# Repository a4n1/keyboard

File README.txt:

Low-profile, diode-less, 36-key, Bluetooth keyboard. Designed with Ergogen and Kicad.

Prerequisites:
nix

Build PCB files:
nix run

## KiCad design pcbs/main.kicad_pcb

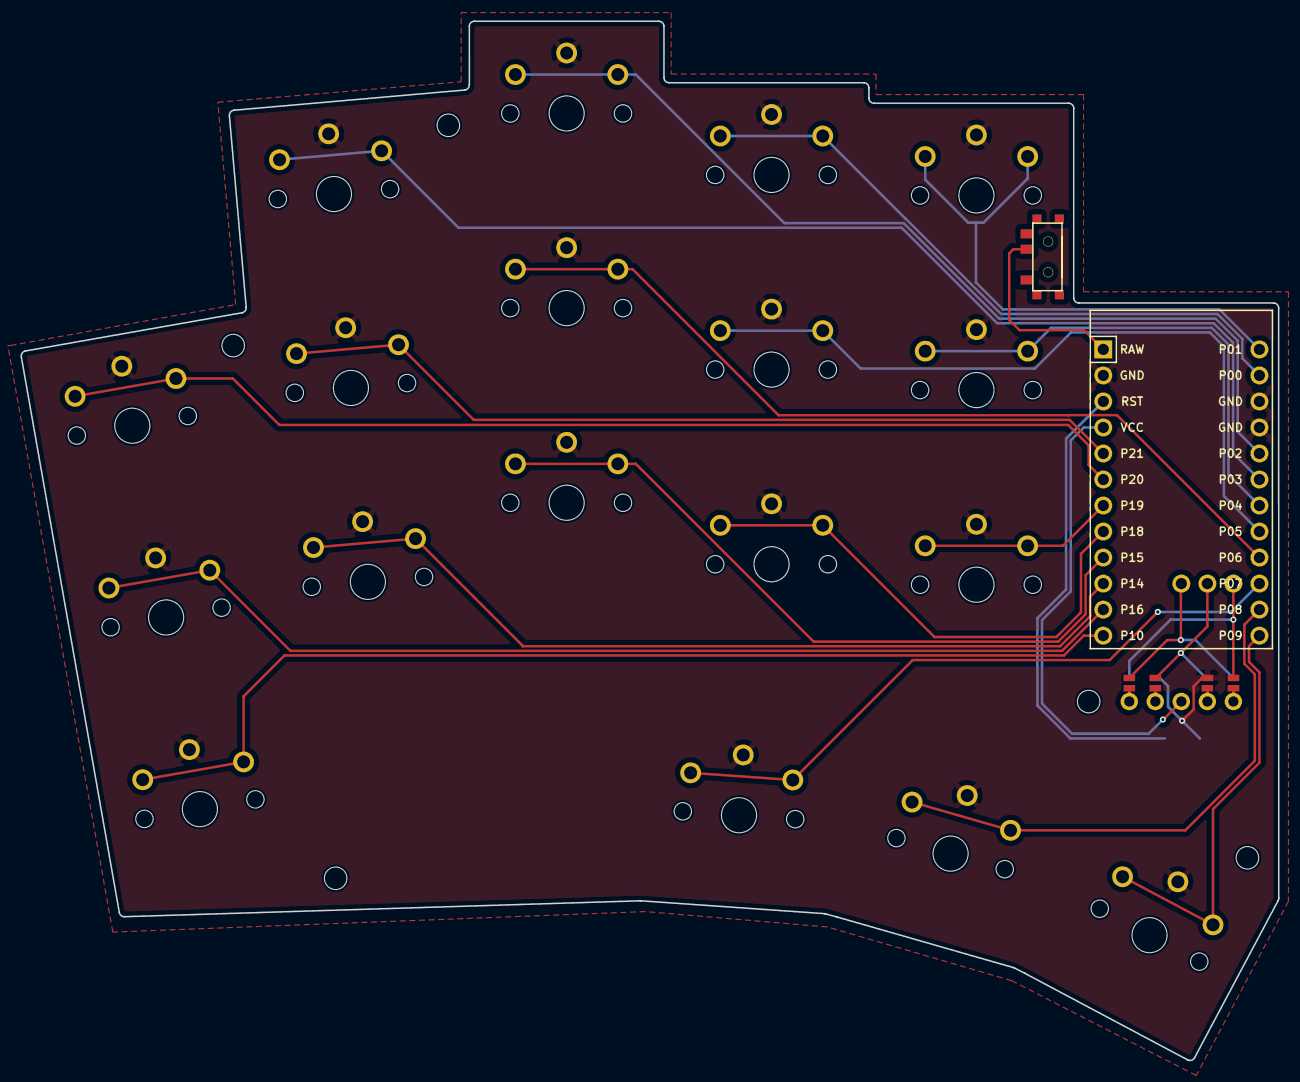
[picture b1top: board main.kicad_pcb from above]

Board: 2 copper layers, 122.7 x 101.4 mm, 21 parts (0 on the bottom side), 24 nets.

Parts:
MCU1: ProMicro
S1, S2, S3, S4, S5, S6, S7, S8, S9, S10, S11, S12, S13, S14, S15, S16, S17, S18: PG1350
T1: SPDT_C128955
nice!view1: nice!view; niceview

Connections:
CS: MCU1.31, nice!view1.1, nice!view1.5
GND: MCU1.2, MCU1.15, MCU1.16, S1.2, S2.2, S3.2, S4.2, S5.2, S6.2, S7.2, S8.2, S9.2, S10.2, S11.2, S12.2, S13.2, S14.2, S15.2, S16.2, S17.2, S18.2, nice!view1.2, nice!view1.4
MOSI: MCU1.33, nice!view1.1, nice!view1.5
RAW: MCU1.1, T1.2
SCK: MCU1.32, nice!view1.2, nice!view1.4
VCC: MCU1.4, nice!view1.3
keys_index_bottom: MCU1.8, S10.1
keys_index_home: MCU1.20, S11.1
keys_index_top: MCU1.14, S12.1
keys_inner_bottom: MCU1.7, S13.1
keys_inner_home: MCU1.19, S14.1
keys_inner_top: MCU1.13, S15.1
keys_middle_bottom: MCU1.9, S7.1
keys_middle_home: MCU1.21, S8.1
keys_middle_top: MCU1.17, S9.1
keys_pinky_bottom: MCU1.12, S1.1
keys_pinky_home: MCU1.11, S2.1
keys_pinky_top: MCU1.6, S3.1
keys_ring_bottom: MCU1.10, S4.1
keys_ring_home: MCU1.5, S5.1
keys_ring_top: MCU1.18, S6.1
keys_thumb_home: MCU1.23, S17.1
keys_thumb_inner: MCU1.22, S16.1
keys_thumb_outer: MCU1.24, S18.1

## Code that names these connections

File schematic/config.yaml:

meta:
  engine: 4.1.0
points:
  zones:
    keys:
      columns:
        pinky:
          key:
            splay: 10
        ring:
          key:
            stagger: 19 
            spread: 20 
            splay: -5
        middle:
          key:
            stagger: 6
            spread: 20 
            splay: -5
        index:
          key:
            stagger: -6
            spread: 20 
        inner:
          key:
            stagger: -2
            spread: 20 
      rows:
        bottom:
        home:
        top:
      anchor:
        shift: [150, -150]
    thumb:
      anchor:
        ref: keys_inner_bottom
        shift: [-1.2875cx, -1.25cx]
      columns:
        inner:
          key:
            splay: -4
            name: keys_thumb_inner
        home:
          key:
            splay: -12
            origin: [-10, -10]
            name: keys_thumb_home
        outer:
          key:
            splay: -12
            origin: [-10, -10]
            name: keys_thumb_outer
outlines:
  panel:
    - what: polygon
      operation: stack
      fillet: 0.5
      points:
        - ref: keys_pinky_top
          shift: [-0.5cx - 0.5, -0.5cx]
        - ref: keys_pinky_top
          shift: [-0.5cx - 0.5, 0.5cx]
        - ref: keys_pinky_top
          shift: [0.5cx + 3.915, 0.5cx]
        - ref: keys_ring_top
          shift: [-0.5cx - 0.5, 0.5cx]
        - ref: keys_ring_top
          shift: [0.5cx + 5.05, 0.5cx]
        - ref: keys_middle_top
          shift: [-0.5cx - 0.5, 0.5cx]
        - ref: keys_middle_top
          shift: [0.5cx + 0.5, 0.5cx]
        - ref: keys_index_top
          shift: [-0.5cx - 1.5, 0.5cx]
        - ref: keys_index_top
          shift: [0.5cx + 0.5, 0.5cx]
        - ref: keys_inner_top
          shift: [-0.5cx - 1.5, 0.5cx]
        - ref: keys_inner_top
          shift: [0.5cx + 0.5, 0.5cx]
        - ref: keys_inner_top
          shift: [0.5cx + 0.5, -0.5cx - 1.5]
        - ref: keys_inner_top
          shift: [1.5cx + 2.5, -0.5cx - 1.5]
        - ref: keys_thumb_outer
          shift: [0.5cx + 0.5, 0.5cx]
        - ref: keys_thumb_outer
          shift: [0.5cx + 0.5, -0.5cx]
        - ref: keys_thumb_outer
          shift: [-0.5cx, -0.5cx]
        - ref: keys_thumb_home
          shift: [0.5cx, -0.5cx]
        - ref: keys_thumb_home
          shift: [-0.5cx, -0.5cx]
        - ref: keys_thumb_inner
          shift: [0.5cx, -0.5cx]
        - ref: keys_thumb_inner
          shift: [-0.5cx, -0.5cx]
        - ref: keys_pinky_bottom
          shift: [-0.5cx - 0.5, -0.5cx]
pcbs:
  main:
    template: kicad8
    outlines:
      main:
        outline: panel
    footprints:
      choc_hotswap:
        what: choc
        where: true
        params:
          from: "{{name}}"
          to: GND
          keycaps: true
          reverse: true
          hotswap: false
      controller:
        what: nicenano
        where:
          - ref: keys_inner_bottom
            shift: [cx + 2, 0.5cx]
            rotate: -90
        params:
          P20: keys_pinky_top
          P16: keys_pinky_home
          P10: keys_pinky_bottom

          P3: keys_ring_top
          P21: keys_ring_home
          P14: keys_ring_bottom

          P2: keys_middle_top
          P6: keys_middle_home
          P15: keys_middle_bottom

          P0: keys_index_top
          P5: keys_index_home
          P18: keys_index_bottom

          P1: keys_inner_top
          P4: keys_inner_home
          P19: keys_inner_bottom

          P7: keys_thumb_inner
          P8: keys_thumb_home
          P9: keys_thumb_outer

          P33: MOSI
          P32: SCK
          P31: CS
      niceview:
        what: niceview
        where:
          ref:
            - keys_inner_bottom
          shift: [0.5cx + 5.92, -0.5cx - 4]
          rotate: 90
        params:
          CS: CS
          SCK: SCK
          MOSI: MOSI
      reset:
        what: reset
        where:
          ref:
            - keys_inner_bottom
          shift: [0.5cx + 11.1, -0.5cx - 6]
          rotate: 180 
        params:
          from: RST
          to: GND
      power:
        what: slider
        where:
          ref: keys_inner_top
          shift: [0.5cx - 2, -6]
          rotate: -90
        params:
          side: F
          from: B+
          to: RAW

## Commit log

2026-01-02 init
